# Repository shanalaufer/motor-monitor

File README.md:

# Motor Health Monitor
### AI-powered predictive maintenance system for electric motors

👉 [API docs (Swagger UI)](https://motor-fault-api-f7r8.onrender.com/docs)

---

## What this is

An end-to-end system that detects motor bearing faults before they cause failure. It collects vibration data from an accelerometer, extracts signal features using FFT-based processing, and runs a machine learning model to classify motor health in real time — displayed on a live web dashboard.

This is the same concept used in industrial predictive maintenance systems at manufacturing plants, wind farms, and data centers — where unplanned motor failures can cost thousands of dollars per minute of downtime.

---

## Live demo

👉 [Open the live dashboard](https://motor-monitor-gtmdausuctqgflvd5xteux.streamlit.app/)

Use the sidebar to switch between healthy and faulty motor modes and watch the FFT, health score, and status banner update in real time.

---

## System architecture
```
Vibration sensor (MPU-6050)
        ↓
Edge node (ESP32) — samples at 500Hz over I2C
        ↓
Feature extraction — FFT, RMS, crest factor, fault frequency energy
        ↓
REST API (FastAPI) — hosted on Render
        ↓
Random Forest + Autoencoder — dual model inference
        ↓
Live dashboard (Streamlit Cloud) — health score, signal plots, alerts
```

---

## Key results

- 96.7% accuracy (RF) and 90.0% accuracy (AE) on 297 real motor samples
- Health score drops from 95-100% to 0-43% when physical imbalance introduced
- Top features: crest_factor (31%), RMS (30%)
- Fault detection latency: <2 seconds from sensor to alert
- Autoencoder trained on healthy samples only — detects faults via reconstruction error
- 3-axis preprocessing: Butterworth bandpass (10-200Hz) + Welch PSD axis selection

---
## Model comparison — Random Forest vs Autoencoder

| | Random Forest | Autoencoder |
|---|---|---|
| Type | Supervised | Unsupervised |
| Training data needed | Labeled healthy + faulty | Healthy only |
| Accuracy | 96.7% | 90.0% |
| Missed faults | 0 | 0 |
| False alarms | 0 | 1 |
| Faulty error ratio | N/A | 36.9x higher than healthy |

**Key insight:** The autoencoder was trained only on healthy samples — it never saw a single fault example. Yet it detected faulty motors with high accuracy because the reconstruction error for faulty signals was significantly higher than healthy signals.

**Reconstruction error ratio after retraining (v1 model — historical):**
After collecting more healthy data (48 → 106 samples) and retraining, the ratio dropped from 66x to 36.9x — but the system became significantly more reliable on the live motor. Healthy reconstruction error dropped from 0.53 to 0.18, meaning the model learned a tighter, more accurate definition of normal. The tradeoff between sensitivity and false alarm rate is a core challenge in anomaly detection — more healthy data improved real-world reliability at the cost of a slight reduction in the error ratio.

**Unexpected finding:** Energy at 100Hz was actually higher in healthy motors (0.385) than faulty ones (0.290) — the opposite of what simulation predicted. Real motor behavior doesn't always match simulation assumptions. This is why collecting real labeled data matters.

**Why the autoencoder matters for real deployment:** A Random Forest requires fault examples to train on — meaning you need to wait for something to break or deliberately damage equipment. The autoencoder only needs normal operation data, which every system already has from day one.

## API layer

The system runs as three separate services communicating through a REST API:
ESP32 → receiver.py → POST /predict → api.py → stores result
↓
dashboard.py → GET /health every 2s → live display

**API endpoints:**

| Endpoint | Method | What it does |
|---|---|---|
| `/` | GET | Confirms API is running |
| `/health` | GET | Returns latest motor reading |
| `/history` | GET | Returns last 100 readings |
| `/predict` | POST | Accepts features, runs both models, returns results |
| `/faults` | GET | Returns all fault detection events |
| `/trends?hours=24` | GET | Average health scores over a time period |
| `/stats` | GET | Total readings, fault counts, first/last reading time |
| `/export/csv` | GET | Download full history as CSV |

**How to run the system:**

The API is deployed on Render at: https://motor-fault-api-f7r8.onrender.com

To run the system:
- python3 receiver.py — streams ESP32 data to the hosted API
- streamlit run dashboard.py — starts the local dashboard

**Dashboard modes:**
- **Live sensor** — reads from ESP32 via receiver.py → api.py
- **Simulation** — generates signals locally, sends through API for prediction

## How it works

**Signal processing:**
Motor vibration is sampled at 500Hz across all 3 axes (X, Y, Z), preprocessed with DC offset removal, a Butterworth bandpass filter (10-200Hz), and Welch PSD axis selection. The FFT decomposes the raw signal into frequency components — a healthy motor shows one dominant peak at its rotation frequency (50Hz). Motor imbalance creates energy at harmonics of the rotation frequency (100Hz, 150Hz) and elevated crest factor — detected by the ML model in real time. Five features are extracted from each signal window: RMS amplitude, peak value, crest factor, and energy at 50Hz, 100Hz, and 150Hz.

**Machine learning:**
A Random Forest classifier (100 trees) was trained on 1000 labeled samples — 500 healthy, 500 faulty — with an 80/20 train/test split. The model outputs a fault probability which is converted to a 0-100% health score. The model was chosen for its interpretability and robustness on small tabular datasets.

**Why crest factor matters:**
Bearing faults create sharp impact spikes in the vibration signal. Crest factor (peak ÷ RMS) is sensitive to these spikes — a healthy motor has a crest factor around 1.4, while an impact-type fault can push it above 3.0. This is a standard diagnostic metric in industrial vibration analysis.

---
## Hardware integration

The system runs on an ESP32-WROOM microcontroller connected to an MPU-6050 MEMS accelerometer over I2C. The ESP32 samples vibration at 500Hz and streams data over WiFi to the Python pipeline in real time.

**Hardware stack:**
- ESP32-WROOM — microcontroller running MicroPython, handles I2C and WiFi
- MPU-6050 — 3-axis MEMS accelerometer, mounted directly on motor body
- L298N — motor driver module, controls DC motor speed and direction
- Small DC hobby motor — test subject for vibration analysis

**PCB Design:**
Custom PCB designed in KiCad to replace the breadboard prototype. The schematic includes all three main components (ESP32-WROOM-32E, MPU-6050, L298N) with proper decoupling capacitors and power distribution. KiCad design files are included in the `motor monitor pcb/` folder.

**Signal conditioning:**
A hardware RC anti-aliasing filter (R = 10kΩ, C = 68nF, fc = 234Hz) sits between the sensor output and the ESP32 ADC input. This prevents frequency aliasing by attenuating signals above the Nyquist frequency (250Hz at 500Hz sampling rate) before digitization — a problem that cannot be corrected in software after sampling. This complements the software Butterworth bandpass filter in the preprocessing pipeline. Two-stage filtering: hardware prevents aliasing, software removes noise.

**What I learned from real hardware:**

The sim-to-real gap is real. The simulation-trained model performed reasonably on real data but highlighted two key challenges:

1. **Gravity offset** — the accelerometer measures 1g of gravity as a DC offset that needed to be removed before feature extraction using mean subtraction
2. **Fault signature differences** — simulated bearing faults (clean 120Hz sine wave) don't perfectly match real imbalance faults, which show up more in crest factor than in fault frequency energy

**Update:** Real labeled data was collected from the physical motor — 66 healthy samples and 57 faulty samples (imbalance created by asymmetric mass on shaft). Model retrained on real data achieved 100% accuracy with crest factor as the most important feature.

## Results on real hardware

**Healthy motor:** 95-100% health score consistently with sensor mounted on motor body

**Fault detection:** Physical imbalance (asymmetric mass on shaft) successfully detected — system flagged FAULT DETECTED with health score dropping significantly

**Key finding — sim-to-real gap:** Original model trained on simulated 120Hz bearing fault signal did not generalize to real imbalance faults. Real imbalance creates energy at harmonics of rotation frequency (100Hz, 150Hz) and elevated crest factor — not a clean 120Hz signal. Model was retrained with updated imbalance simulation and successfully detected real physical faults.

**Lesson:** The gap between simulation and real sensor data is a genuine engineering challenge. Gravity offset removal, consistent sensor mounting, and fault-type-specific feature engineering were all required to bridge it.

## Tech stack

| Layer | Technology |
|---|---|
| Signal processing | Python, NumPy, SciPy (FFT) |
| Machine learning | scikit-learn (Random Forest) |
| Deep learning | PyTorch (Autoencoder) |
| Edge firmware | MicroPython on ESP32 |
| Sensor | MPU-6050 accelerometer over I2C |
| Backend API | FastAPI |
| Database | SQLite (via Render) |
| Dashboard | Streamlit |
| Deployment | Streamlit Cloud + Render |

---

## Project structure
```
motor-monitor/
├── signal_sim.py          # Signal simulation and FFT visualization
├── generate_dataset.py    # Dataset generation (1000 labeled samples)
├── train_model.py         # Model training and evaluation (simulation)
├── train_real.py          # Retrain on real motor data
├── train_v2.py            # Retrain on preprocessed 3-axis data
├── receiver.py            # Receives ESP32 data, runs ML model
├── dashboard.py           # Live Streamlit dashboard
├── preprocessor.py        # 3-axis preprocessing pipeline
├── autoencoder.py         # PyTorch autoencoder training
├── api.py                 # FastAPI backend
├── motor_dataset.csv      # Generated training dataset
├── real_data.csv          # Real motor sensor data (labeled)
├── real_data_v2.csv       # 297 samples (202 healthy + 95 faulty)
├── raw_healthy.npy        # Raw 3-axis healthy bursts
├── raw_faulty.npy         # Raw 3-axis faulty bursts
├── motor_model.pkl        # Trained Random Forest model
├── autoencoder.pth        # Trained autoencoder weights
├── scaler.pkl             # Feature scaler for autoencoder
├── motor_model_v2.pkl         # RF v2 model
├── autoencoder_v2.pth         # AE v2 weights
├── scaler_v2.pkl              # Feature scaler v2
├── autoencoder_threshold_v2.pkl  # AE threshold v2
└── requirements.txt       # Python dependencies

```
---

## Testing & reliability

The project includes a full automated test suite covering the live API, the preprocessing pipeline, and the ML models — 121 tests across three files. Tests run against the real deployed API on Render and against locally loaded model files, so they catch both integration regressions and model behaviour changes. All three suites pass cleanly and can be run independently or together.

| Test file | Tests | Covers |
|---|---|---|
| `test_api.py` | 39 | All API endpoints — status codes, response shape, field validation, fault classification correctness, DB persistence, CSV export |
| `test_preprocessor.py` | 49 | Raw data shape, DC removal, bandpass filter passband/stopband behaviour, axis selection, feature extraction correctness, CSV output |
| `test_models.py` | 33 | Model loading, RF output format, accuracy regression, feature importance, autoencoder forward pass, reconstruction error ratio, scaler behaviour |

**Signal quality monitoring**

`receiver.py` validates every incoming burst across 6 checks before it reaches the feature extraction pipeline. A burst that fails any check is logged and discarded — it is never posted to the API. This prevents corrupted or disconnected-sensor data from polluting the database or triggering false fault alerts.

- **Too short** — fewer than 64 samples on any axis
- **Flat signal / sensor disconnect** — standard deviation below 0.001 on all three axes simultaneously
- **Excessive noise** — RMS above 20.0 on any axis
- **Clipping** — more than 5% of samples at the ADC's min or max value
- **NaN or Inf** — any non-finite value anywhere in the burst
- **Sampling instability** — burst length deviates more than 10% from the expected 256 samples

**Structured logging**

`receiver.py` logs every event to both stdout and a rotating log file (`receiver.log`) using Python's built-in `logging` module. Each line is timestamped with log level — `INFO` for normal operation, `WARNING` for QC skips and API errors, `ERROR` for main loop exceptions. The file handler rotates at 1MB and keeps 3 backups, so it never fills the disk on a long-running deployment.

**Run all tests:**
```bash
pytest test_api.py test_preprocessor.py test_models.py -v
```

---

## Project roadmap

### Phase 1 — Proven prototype (complete)
- Signal simulation and FFT feature extraction
- Random Forest classifier — 100% accuracy on simulated data
- Streamlit dashboard deployed publicly
- ESP32 + MPU-6050 hardware integration
- Real data collection and model retraining on physical motor
- PyTorch autoencoder — 99% accuracy, unsupervised anomaly detection
- FastAPI REST backend — dual model inference pipeline

### Phase 2 — Better signal pipeline (complete)
- ✅ Hardware validation — test live dashboard with ESP32
- ✅ 3-axis raw data collection (202 healthy + 95 faulty)
- ✅ Butterworth bandpass filter + Welch PSD preprocessing
- ✅ Retrained RF (96.7%) and AE (90.0%) on clean preprocessed data
- ✅ KiCad custom PCB design

### Phase 3 — Product-like system (in progress)
- ✅ Deploy FastAPI to cloud (Render)
- ✅ Update public Streamlit URL to use hosted API
- ✅ Database backend — every prediction persisted to `motor_readings.db` on Render
- ✅ `GET /faults` — all fault detection events
- ✅ `GET /trends?hours=24` — average health over a time period
- ✅ `GET /stats` — total readings, fault counts, first/last reading time
- ✅ `GET /export/csv` — download full history as CSV
- ✅ Dashboard sidebar buttons to load stats, fault log, and 24hr trends
- Multi-node support — monitor multiple motors simultaneously

### Phase 4 — Advanced engineering (future)
- Multiple fault types — bearing defect, imbalance, misalignment
- Multiclass classification
- LLM natural language interface via Anthropic API

---

## Background

Built as a portfolio project to demonstrate the intersection of electrical engineering and machine learning. Predictive maintenance is one of the most widely deployed industrial AI applications — the same signal processing and anomaly detection concepts used here are applied at scale in manufacturing, energy, and aerospace.

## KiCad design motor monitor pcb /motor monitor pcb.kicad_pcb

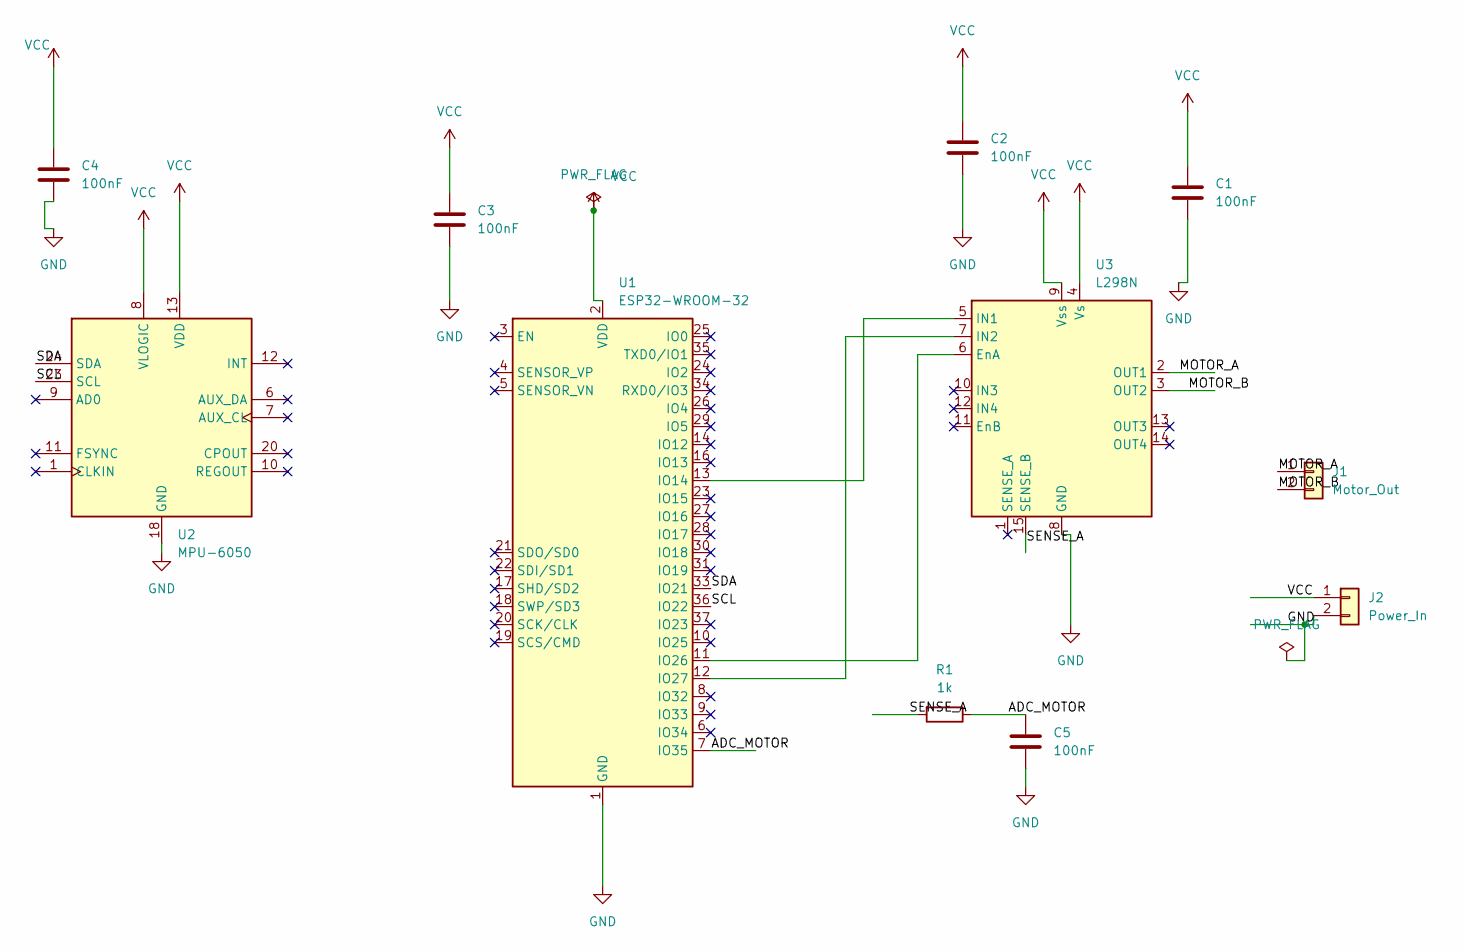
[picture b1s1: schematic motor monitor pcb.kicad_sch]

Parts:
C1, C2, C3, C4, C5: 100nF; C_Disc_D5.0mm_W2.5mm_P5.00mm
J1: Motor_Out; PinHeader_1x02_P2.54mm_Vertical
J2: Power_In; PinHeader_1x02_P2.54mm_Vertical
R1: 1k; R_Axial_DIN0207_L6.3mm_D2.5mm_P10.16mm_Horizontal
U1: ESP32-WROOM-32
U2: MPU-6050; InvenSense_QFN-24_4x4mm_P0.5mm
U3: L298N; TO-220-15_P2.54x5.08mm_StaggerOdd_Lead4.58mm_Vertical

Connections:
/ADC_MOTOR: C5.1, R1.1, U1.7 (IO35)
/MOTOR_A: J1.1, U3.2 (OUT1)
/MOTOR_B: J1.2, U3.3 (OUT2)
/SCL: U1.36 (IO22), U2.23 (SCL)
/SDA: U1.33 (IO21), U2.24 (SDA)
/SENSE_A: R1.2, U3.15 (SENSE_B)
GND: C1.2, C2.2, C3.2, C4.2, C5.2, J2.2, U1.1 (GND), U1.15 (GND), U1.38 (GND), U1.39 (GND), U2.18 (GND), U3.8 (GND)
unnamed: U1.13 (IO14), U3.5 (IN1)
unnamed: U1.11 (IO26), U3.6 (EnA)
unnamed: U1.12 (IO27), U3.7 (IN2)
VCC: C1.1, C2.1, C3.1, C4.1, J2.1, U1.2 (VDD), U2.8 (VLOGIC), U2.13 (VDD), U3.4 (Vs), U3.9 (Vss)

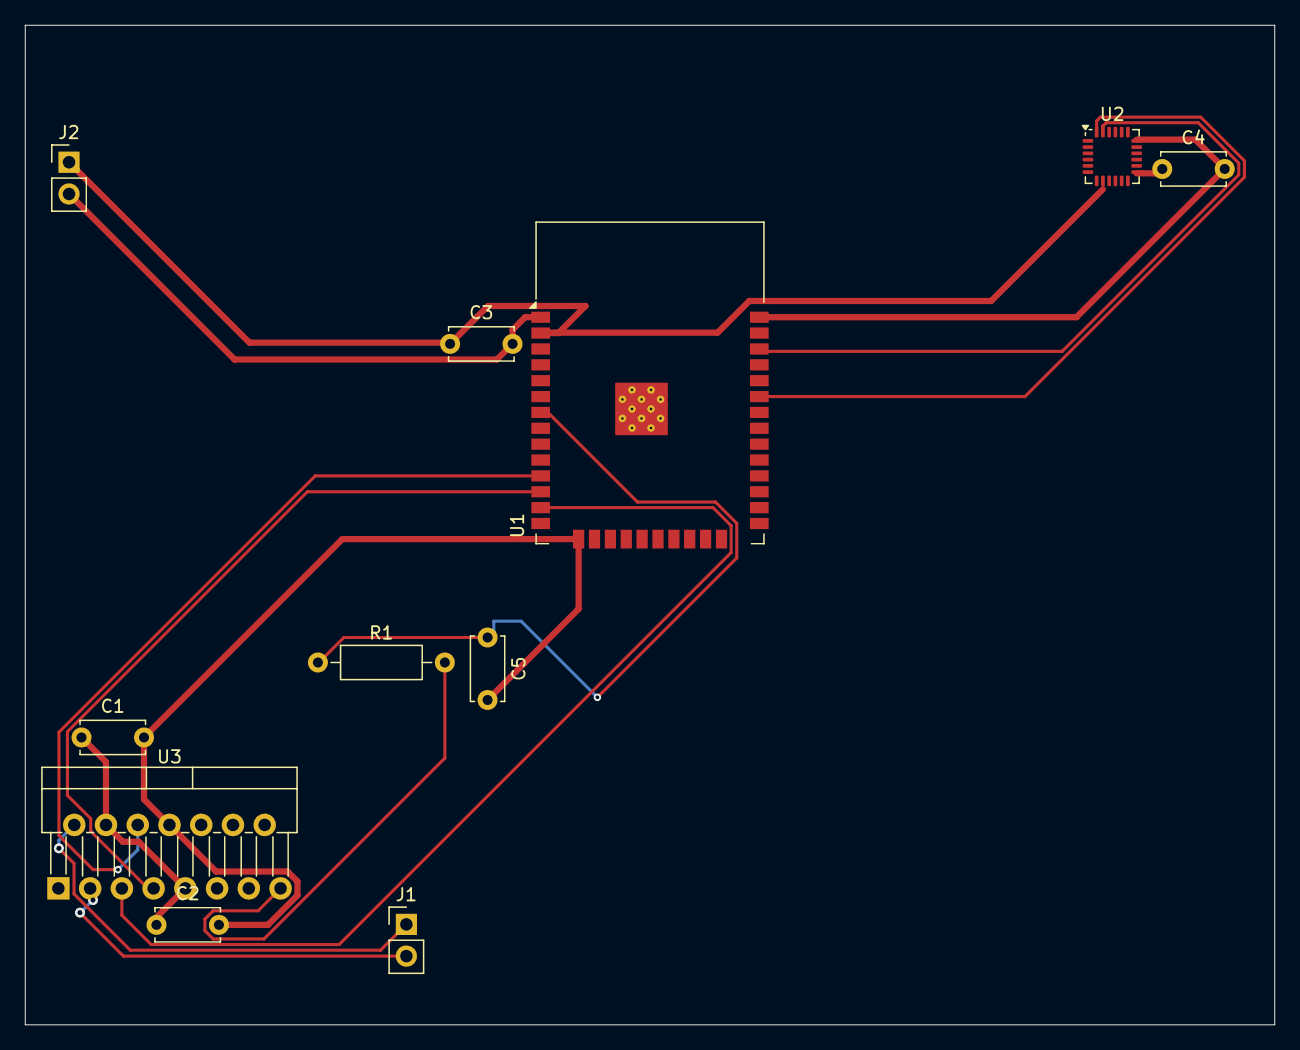
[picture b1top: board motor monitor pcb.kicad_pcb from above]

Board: 2 copper layers, 100.0 x 80.0 mm, 11 parts (0 on the bottom side), 11 nets.

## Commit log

2026-03-18 Phase 1 and 2 complete — signal simulation, dataset, ML model, and dashboard
2026-03-19 Add requirements.txt for Streamlit Cloud deployment
2026-03-19 Fix requirements.txt version conflicts
2026-03-19 Fix Python and package versions for deployment
2026-03-19 Fix streamlit and altair versions
2026-03-19 Add runtime.txt to force Python 3.11
2026-03-19 Fix line_chart height parameter compatibility
2026-03-19 Pin altair to compatible version
2026-03-24 Add README
2026-03-27 Add real hardware integration — ESP32 + MPU-6050 sensor reading live data
2026-03-29 Fix Streamlit URL in README
2026-03-29 Real sensor data flowing — ESP32 + MPU-6050 sending live vibration readings to ML pipeline
2026-03-30 Add hardware integration — ESP32 + MPU-6050 streaming real data
    - sensor.py auto-starts motor on boot
    - receiver.py removes gravity offset and saves real data to CSV
    - README documents sim-to-real gap and hardware stack
2026-03-30 Update fault model — imbalance simulation with 100Hz and 150Hz harmonics, retrain
2026-04-05 Add real motor data — first successful fault detection
2026-04-05 Update README with real hardware results and fault detection success
2026-04-10 Retrain model on real motor data — 100% accuracy on physical imbalance detection
2026-04-10 Update README to reflect real hardware results and retrained model
2026-04-10 Add PyTorch autoencoder — 99% accuracy unsupervised, faulty error 66x higher than healthy
2026-04-10 Add model comparison and key insights to README
2026-04-10 Add FastAPI backend + update dashboard with dual model display and API integration
2026-04-12 Update requirements.txt with fastapi, uvicorn, torch
2026-04-12 Clean up README — fix architecture, sampling rate, tech stack, project structure, roadmap heading
2026-04-13 Add KiCad PCB schematic, screenshot, and README documentation including anti-aliasing filter design
2026-04-13 Add .gitignore, clean up repo
2026-04-15 Add PCB layout - components placed
    Footprints assigned, board outline set, all components
    placed and ready for routing. Schematic also finalized
    with RC anti-aliasing filter added.
2026-04-15 update gitignore
2026-04-16 Add ESP32 firmware files in firmware/ folder
2026-04-17 Retrain autoencoder with more healthy data — 96% accuracy, fix AE false positives on live motor
2026-04-17 Update README with retrained autoencoder results — 96% accuracy, 36.9x ratio
2026-04-17 Add Procfile and update dashboard API URL for Render deployment
2026-04-17 fix Render Python version and torch compatibility
2026-04-17 Update README to reflect Render deployment
2026-04-17 Add 3-axis data collection and preprocessing pipeline foundation - sensor.py: stream X, Y, Z axes instead of Z only - receiver.py: parse 3-axis payload, save to raw_healthy.npy/raw_faulty.npy, log to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
2026-04-24 Collect 3-axis raw motor data: 202 healthy + 95 faulty bursts
2026-04-24 Upgrade to v2 models: 3-axis preprocessed data, RF 96.7%, AE 90.0%
2026-04-24 update dashboard and readme
2026-04-25 PCB routing in progress
2026-04-26 fixes in pcb layout
2026-04-30 Fix dashboard: define overall_status before use
2026-04-30 Raise AE threshold to mean+3std for better live stability
2026-05-06 add SQLite database
    store more history
2026-05-24 add db-check endpoint
2026-05-24 add faults, trends, stats endpoints
2026-05-24 dd historical stats, fault log, and trends to sidebar
2026-05-24 fix trends null values when db is empty
2026-05-24 add CSV export endpoint
2026-05-24 update README: fix phases, add new endpoints, clean up tech stack
2026-05-24 Add automated API test suite — 39 tests across all endpoints
2026-05-24 Add preprocessing validation test suite — 49 tests covering pipeline, filter, and feature extraction
2026-05-24 Add model regression test suite — 33 tests covering RF, autoencoder, scaler, and model consistency
2026-05-24 Add signal quality monitoring layer to receiver.py — 6 checks, QC stats, skip reporting
2026-05-24 Add structured logging to receiver.py — timestamps, log levels, rotating file handler
2026-05-24 Add Testing & Reliability section to README — 121 tests, QC monitoring, structured logging
